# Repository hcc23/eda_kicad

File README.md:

eda_kicad
=========

KiCad EDA PCB Projects

# Projects

This repository follows Vincent Driessen's [gitflow branching model](http://nvie.com/git-model/),
so each new addition is initially started as a 'feature'.

* [] Invensense MPU-9150 breakout board

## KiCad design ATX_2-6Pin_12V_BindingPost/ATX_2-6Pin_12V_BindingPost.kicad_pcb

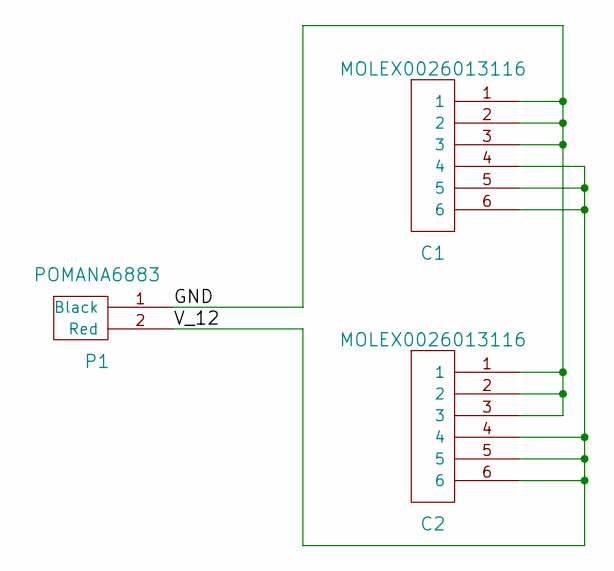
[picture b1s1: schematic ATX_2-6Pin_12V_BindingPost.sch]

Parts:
C1, C2: MOLEX0026013116
P1: POMANA6883

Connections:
/GND: C1.1, C1.2, C1.3, C2.1, C2.2, C2.3, P1.1 (Black)
/V_12: C1.4, C1.5, C1.6, C2.4, C2.5, C2.6, P1.2 (Red)

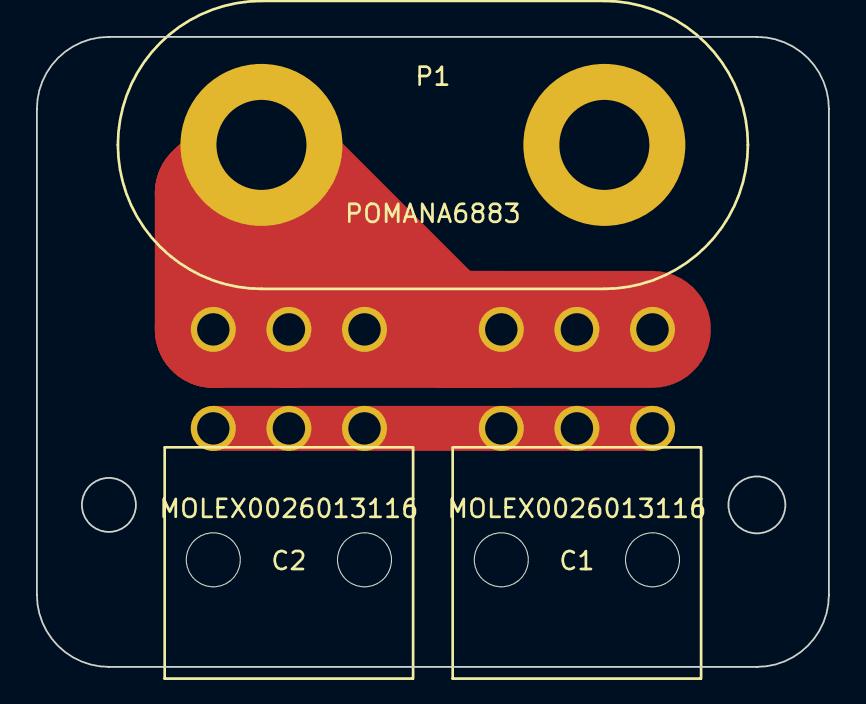
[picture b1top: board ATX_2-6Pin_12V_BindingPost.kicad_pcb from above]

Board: 2 copper layers, 44.0 x 35.0 mm, 3 parts (0 on the bottom side), 2 nets.

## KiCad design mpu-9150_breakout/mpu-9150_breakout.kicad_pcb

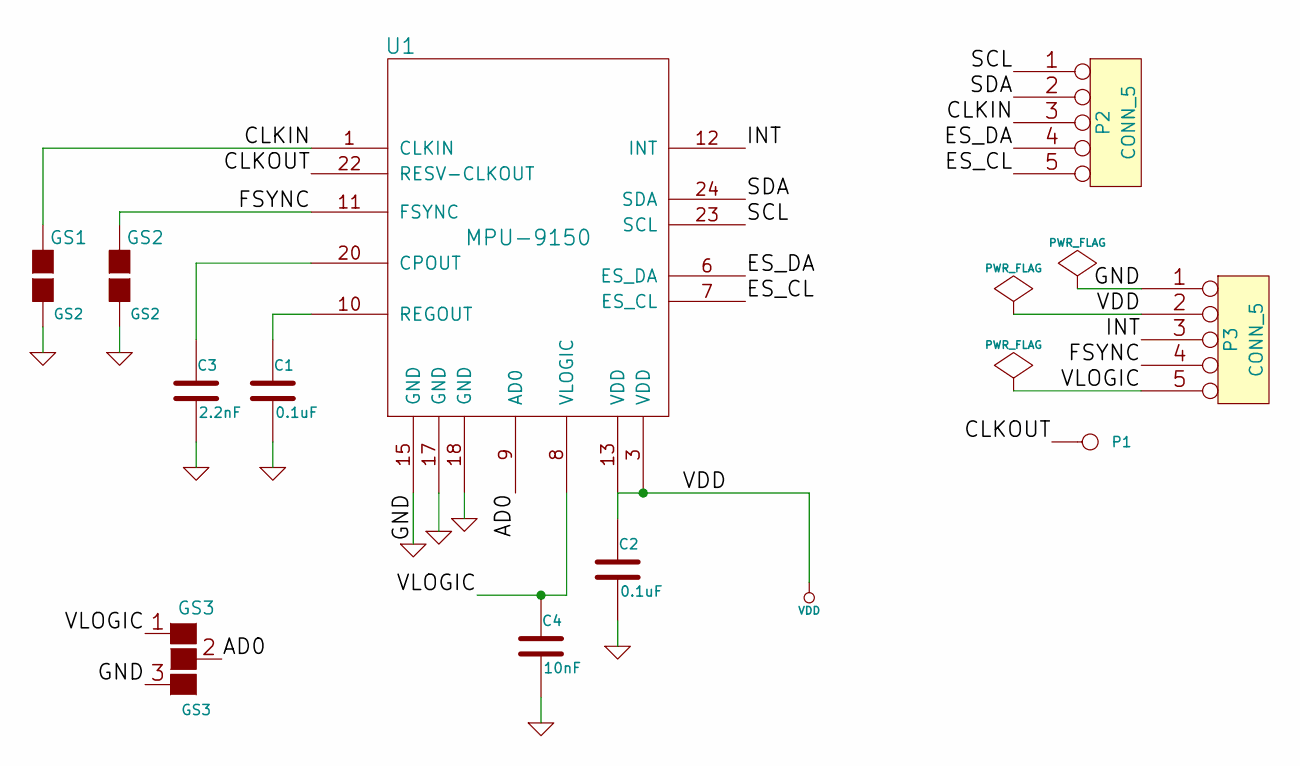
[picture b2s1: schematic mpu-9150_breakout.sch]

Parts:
C1, C2: 0.1uF
C3: 2.2nF
C4: 10nF
GS1, GS2: GS2
GS3: GS3
P1: CONN_1
P2, P3: CONN_5
U1: MPU-9150

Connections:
/AD0: GS3.2 (G2), U1.9 (AD0)
/CLKIN: GS1.1 (G1), P2.3, U1.1 (CLKIN)
/CLKOUT: P1.1, U1.22 (RESV-CLKOUT)
/ES_CL: P2.5, U1.7 (ES_CL)
/ES_DA: P2.4, U1.6 (ES_DA)
/FSYNC: GS2.1 (G1), P3.4, U1.11 (FSYNC)
/INT: P3.3, U1.12 (INT)
/SCL: P2.1, U1.23 (SCL)
/SDA: P2.2, U1.24 (SDA)
/VLOGIC: C4.1, GS3.1 (G1), P3.5, U1.8 (VLOGIC)
GND: C1.2, C2.2, C3.2, C4.2, GS1.2 (G2), GS2.2 (G2), GS3.3 (G3), P3.1, U1.15 (GND), U1.17 (GND), U1.18 (GND)
unnamed: C3.1, U1.20 (CPOUT)
unnamed: C1.1, U1.10 (REGOUT)
VDD: C2.1, P3.2, U1.3 (VDD), U1.13 (VDD)

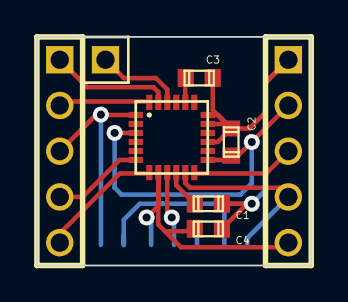
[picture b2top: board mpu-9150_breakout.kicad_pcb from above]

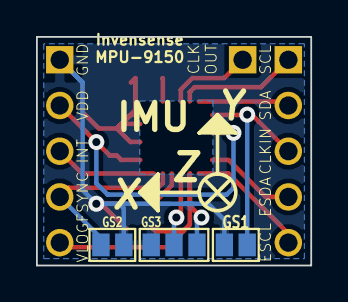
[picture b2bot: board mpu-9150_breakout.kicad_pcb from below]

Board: 2 copper layers, 15.2 x 12.7 mm, 11 parts (3 on the bottom side), 14 nets.

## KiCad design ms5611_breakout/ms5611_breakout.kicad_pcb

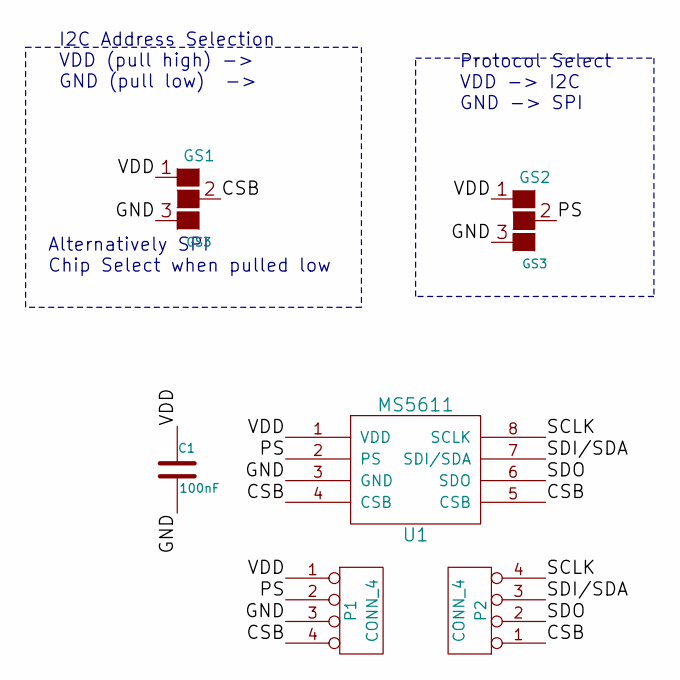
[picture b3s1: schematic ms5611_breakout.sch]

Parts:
C1: 100nF
GS1, GS2: GS3
P1, P2: CONN_4
U1: MS5611

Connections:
/CSB: GS1.2 (G2), P1.4, P2.1, U1.4 (CSB), U1.5 (CSB)
/GND: C1.2, GS1.3 (G3), GS2.3 (G3), P1.3, U1.3 (GND)
/PS: GS2.2 (G2), P1.2, U1.2 (PS)
/SCLK: P2.4, U1.8 (SCLK)
/SDI/SDA: P2.3, U1.7 (SDI/SDA)
/SDO: P2.2, U1.6 (SDO)
/VDD: C1.1, GS1.1 (G1), GS2.1 (G1), P1.1, U1.1 (VDD)

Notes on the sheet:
Protocol Select VDD -> I2C GND -> SPI
I2C Address Selection VDD (pull high) -> GND (pull low) ->
Alternatively SPI Chip Select when pulled low

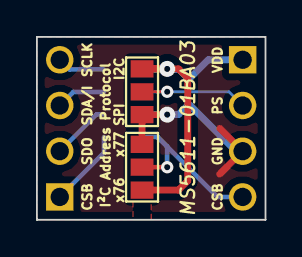
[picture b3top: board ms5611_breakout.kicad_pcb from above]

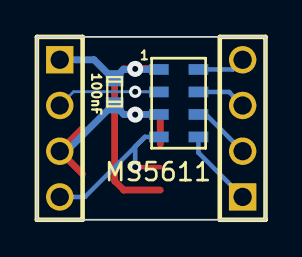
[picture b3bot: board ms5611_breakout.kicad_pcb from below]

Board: 2 copper layers, 12.7 x 10.2 mm, 6 parts (4 on the bottom side), 7 nets.

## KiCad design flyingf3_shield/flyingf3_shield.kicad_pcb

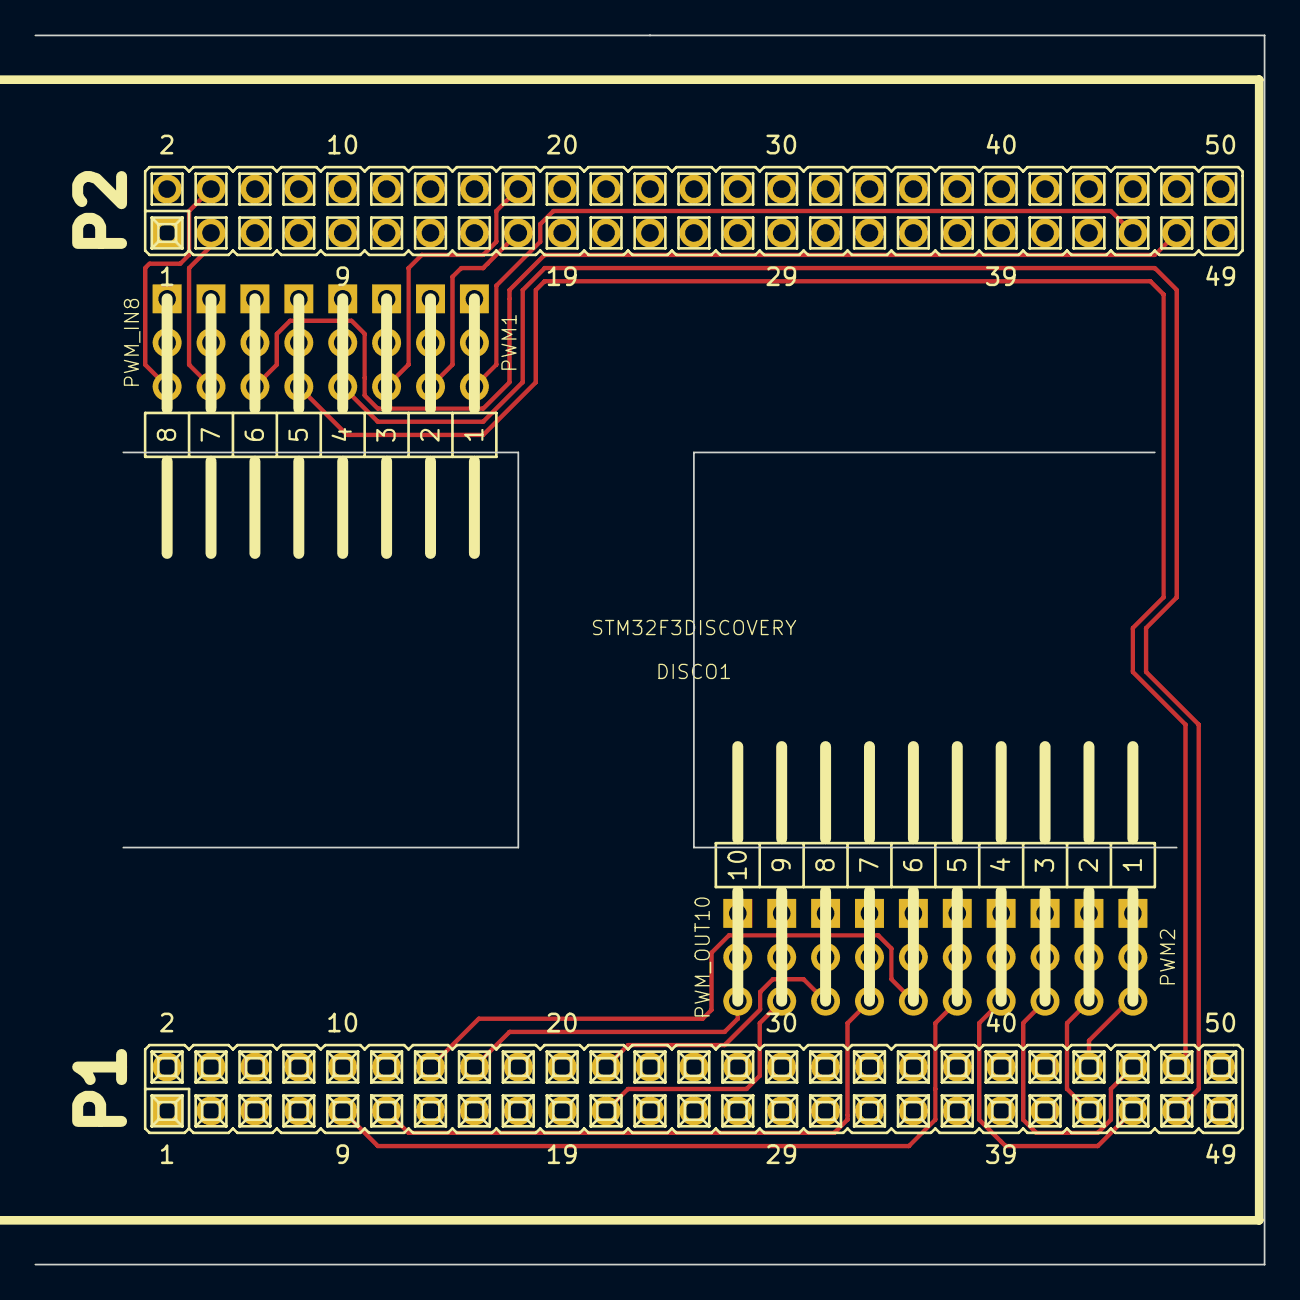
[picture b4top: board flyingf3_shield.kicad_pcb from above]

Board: 2 copper layers, 71.1 x 71.1 mm, 3 parts (0 on the bottom side), 21 nets.

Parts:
DISCO1: STM32F3DISCOVERY; STMF3DISCOVERY
PWM1: PWM_IN8; SERVO-8H-R
PWM2: PWM_OUT10; SERVO-10H-L

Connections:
/GND: DISCO1.49, DISCO1.50, DISCO1.74, DISCO1.75, DISCO1.99, PWM1.1, PWM2.1
/PWM_IN_1: DISCO1.67, PWM1.3
/PWM_IN_2: DISCO1.95, PWM1.4
/PWM_IN_3: DISCO1.96, PWM1.5
/PWM_IN_4: DISCO1.63, PWM1.6
/PWM_IN_5: DISCO1.64, PWM1.7
/PWM_IN_6: DISCO1.65, PWM1.8
/PWM_IN_7: DISCO1.10, PWM1.9
/PWM_IN_8: DISCO1.11, PWM1.10
/PWM_OUT_1: DISCO1.59, PWM2.3
/PWM_OUT_2: DISCO1.60, PWM2.4
/PWM_OUT_3: DISCO1.61, PWM2.5
/PWM_OUT_4: DISCO1.62, PWM2.6
/PWM_OUT_5: DISCO1.24, PWM2.7
/PWM_OUT_6: DISCO1.25, PWM2.8
/PWM_OUT_7: DISCO1.26, PWM2.9
/PWM_OUT_8: DISCO1.35, PWM2.10
/PWM_OUT_9: DISCO1.36, PWM2.11
/PWM_OUT_10: DISCO1.29, PWM2.12
/VCC_3V: DISCO1.6, DISCO1.20
/VCC_5V: DISCO1.21, DISCO1.22

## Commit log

2014-02-09 Initial commit for the Invensense MPU-9150 IMU breakout board
2014-02-09 Reflect start on MPU-9150 breakout board
    Start a projects section, add a note on using gitflow and append
    the mpu9150 breakout board project
2014-02-09 Fix markdown formatting
2014-02-10 Add first pcb layout
2014-02-11 Modify to the version send to OSH Park
2014-02-11 Add missing file
2014-02-12 Add the footprint of the F3DISCOVERY board.
2014-02-12 Add *.bak to the list of ignored files.
2014-02-12 Add *.kicad_pcb-bak to ignored files.
2014-02-12 Initial commit on shield.
2014-02-27 Working on the Shield
2014-03-21 pushing current local state
2014-03-21 Add initial library files for PWM header connectors
2014-03-21 Update gerbers.
2014-03-24 Initial commit of an MS5611 breakout board
    This is an unfinished initial commit of a breakout board. The footprint
    might be in a wrong module and it isn't connected to the net names yet.
2014-04-06 Finish first version of the breakout board.
2014-04-06 Adding Gerber files.
2014-04-06 Correcting Gerbers for OSH Park
    This version got sent to OSH Park. The silk screen had to be changed
    to a min thickness of 5 mills.
2014-07-05 Fixing the 7-bit I2C Address on silk screen
2014-07-16 Adding pin names to silk screen
2014-08-02 Adding a 12V ATX Breakout Board from PCI-E
    This board can take a 8 pin PCI-E power cable from an ATX
    power supply and routes it to a dual binding post.
    It might be necessary to support the connections through extra thick solder
    or an aded single strand copper conductor (preferred over more solder)
2014-08-03 Adding the dual 6-pin version
    And modifying the routing for the 8 pin one.
2014-09-08 Adding 2.4 GHz Patch antenna
2014-09-14 changing vias and mounting slots
